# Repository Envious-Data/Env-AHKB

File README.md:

# Env-AHKB
 A keyboard that uses a HappyHackingKeyBoard inspired layout

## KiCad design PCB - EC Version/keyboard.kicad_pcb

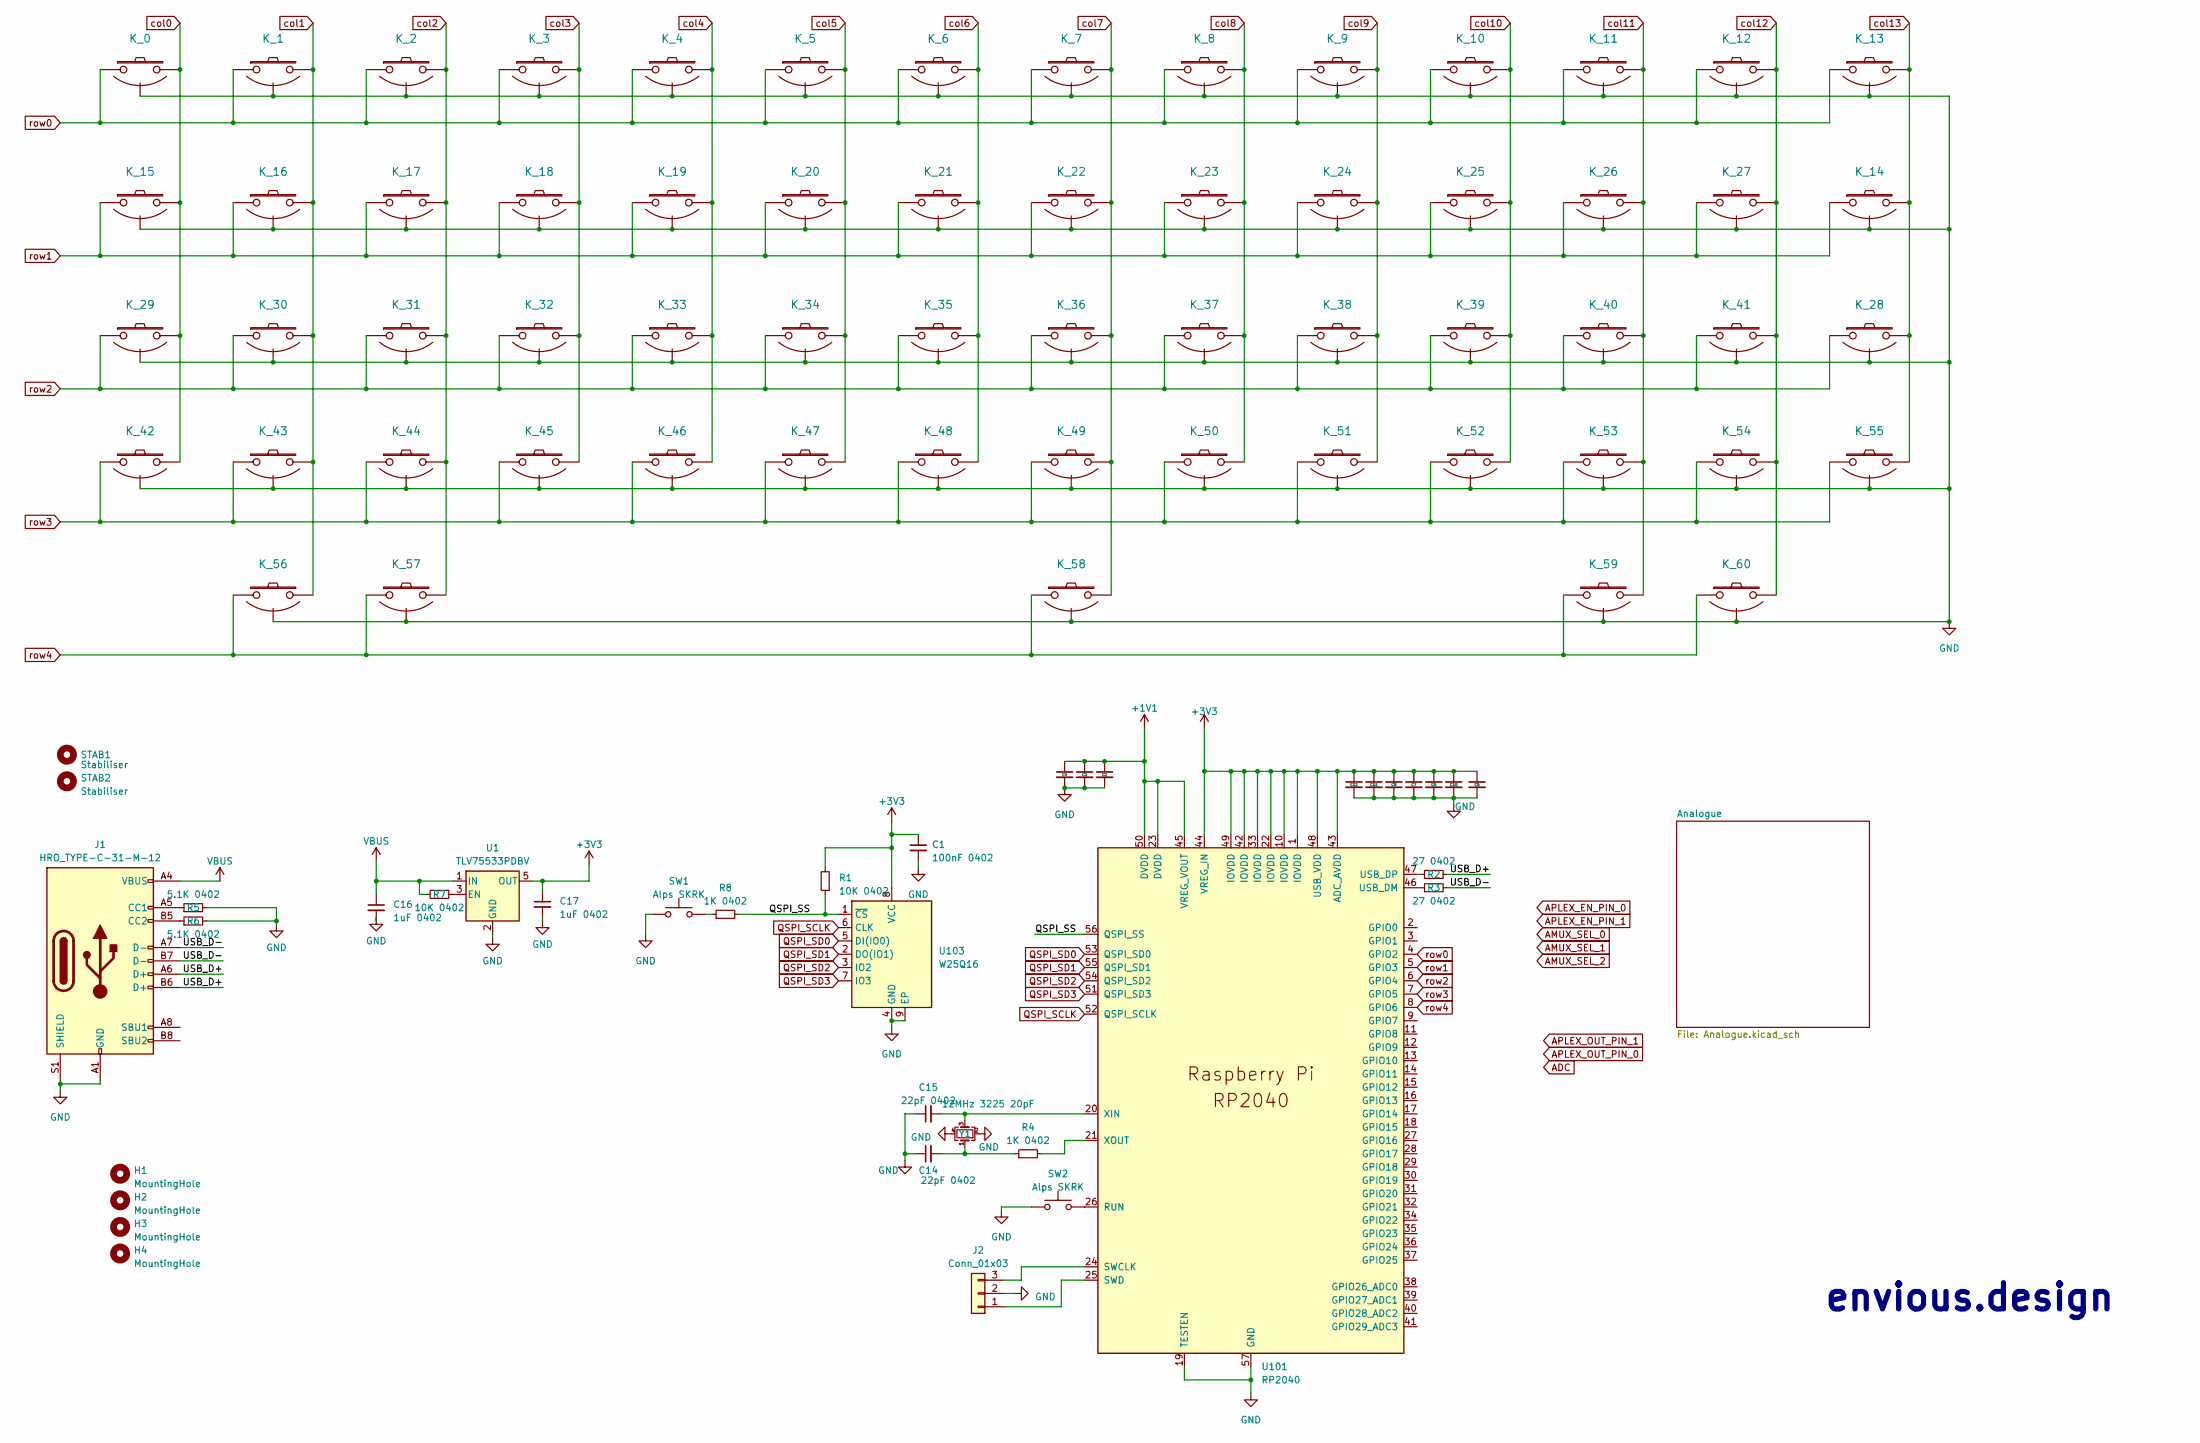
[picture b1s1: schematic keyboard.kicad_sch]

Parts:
C1, C3, C4, C6, C7, C8, C10, C11, C12: 100nF 0402; C_0402_1005Metric
C2, C5, C16, C17: 1uF 0402; C_0402_1005Metric
C14, C15: 22pF 0402; C_0402_1005Metric
H1, H2, H3, H4: MountingHole; MountingHole_3.5mm_Pad
J1: HRO_TYPE-C-31-M-12; USB_C_Receptacle_HRO_TYPE-C-31-M-12
J2: Conn_01x03; PinHeader_1x03_P2.54mm_Vertical
K_0, K_1, K_2, K_3, K_4, K_5, K_6, K_7, K_8, K_9, K_10, K_11, K_12, K_13, K_14, K_15, K_16, K_17, K_18, K_19, K_20, K_21, K_22, K_23, K_24, K_25, K_26, K_27, K_28, K_29, K_30, K_31, K_32, K_33, K_34, K_35, K_36, K_37, K_38, K_39, K_40, K_41, K_42, K_43, K_44, K_45, K_46, K_47, K_48, K_49, K_50, K_51, K_52, K_53, K_54, K_55, K_56, K_57, K_58, K_59, K_60: KEYSW; ecs_pad_1U_no_ring
R1, R7: 10K 0402; R_0402_1005Metric
R2, R3: 27 0402; R_0402_1005Metric
R4, R8: 1K 0402; R_0402_1005Metric
R5, R6: 5.1K 0402; R_0402_1005Metric
STAB1: Stabiliser; Stabilizer_Cherry_MX_7u
STAB2: Stabiliser; Stabilizer_Cherry_MX_2u
SW1, SW2: Alps SKRK; SW_Push_SPST_NO_Alps_SKRK
U1: TLV75533PDBV; SOT-23-5
U101: RP2040; RP2040-QFN-56
U103: W25Q16; SON-8-1EP_3x2mm_P0.5mm_EP1.4x1.6mm
Y1: 12MHz 3225 20pF; Crystal_SMD_3225-4Pin_3.2x2.5mm

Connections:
+1V1: C2.1, C3.1, C4.1, U101.23 (DVDD), U101.45 (VREG_VOUT), U101.50 (DVDD)
/QSPI_SS: R1.1, R8.2, U101.56 (QSPI_SS), U103.1 (~CS)
/USB_D+: J1.A6 (D+), J1.B6 (D+), R2.2
/USB_D-: J1.A7 (D-), J1.B7 (D-), R3.2
GND: C1.2, C2.2, C3.2, C4.2, C5.2, C6.2, C7.2, C8.2, C10.2, C11.2, C12.2, C14.1, C15.1, C16.2, C17.2, J1.A1 (GND), J1.A12 (GND), J1.B1 (GND), J1.B12 (GND), J1.S1 (SHIELD), J2.2, K_0.3 (SG), K_1.3 (SG), K_2.3 (SG), K_3.3 (SG), K_4.3 (SG), K_5.3 (SG), K_6.3 (SG), K_7.3 (SG), K_8.3 (SG), K_9.3 (SG), K_10.3 (SG), K_11.3 (SG), K_12.3 (SG), K_13.3 (SG), K_14.3 (SG), K_15.3 (SG), K_16.3 (SG), K_17.3 (SG), K_18.3 (SG), K_19.3 (SG), K_20.3 (SG), K_21.3 (SG), K_22.3 (SG), K_23.3 (SG), K_24.3 (SG), K_25.3 (SG), K_26.3 (SG), K_27.3 (SG), K_28.3 (SG), K_29.3 (SG), K_30.3 (SG), K_31.3 (SG), K_32.3 (SG), K_33.3 (SG), K_34.3 (SG), K_35.3 (SG), K_36.3 (SG), K_37.3 (SG), K_38.3 (SG), K_39.3 (SG), K_40.3 (SG), K_41.3 (SG), K_42.3 (SG), K_43.3 (SG), K_44.3 (SG), K_45.3 (SG), K_46.3 (SG), K_47.3 (SG), K_48.3 (SG), K_49.3 (SG), K_50.3 (SG), K_51.3 (SG), K_52.3 (SG), K_53.3 (SG), K_54.3 (SG), K_55.3 (SG), K_56.3 (SG), K_57.3 (SG), K_58.3 (SG), K_59.3 (SG), K_60.3 (SG), R5.2, R6.2, SW1.1, SW2.1, U1.2 (GND), U101.19 (TESTEN), U101.57 (GND), U103.4 (GND), U103.9 (EP), Y1.2, Y1.4; also elsewhere on the board
unnamed: C14.2, R4.1, Y1.1
unnamed: J1.A5 (CC1), R5.1
unnamed: J1.B5 (CC2), R6.1
unnamed: J2.1, U101.25 (SWD)
unnamed: J2.3, U101.24 (SWCLK)
unnamed: R8.1, SW1.2
unnamed: R7.1, U1.3 (EN)
unnamed: SW2.2, U101.26 (RUN)
unnamed: R3.1, U101.46 (USB_DM)
unnamed: R2.1, U101.47 (USB_DP)
unnamed: C15.2, U101.20 (XIN), Y1.3
unnamed: R4.2, U101.21 (XOUT)
QSPI_SCLK: U101.52 (QSPI_SCLK), U103.6 (CLK)
QSPI_SD0: U101.53 (QSPI_SD0), U103.5 (DI(IO0))
QSPI_SD1: U101.55 (QSPI_SD1), U103.2 (DO(IO1))
QSPI_SD2: U101.54 (QSPI_SD2), U103.3 (IO2)
QSPI_SD3: U101.51 (QSPI_SD3), U103.7 (IO3)
VBUS: C16.1, J1.A4 (VBUS), J1.A9 (VBUS), J1.B4 (VBUS), J1.B9 (VBUS), R7.2, U1.1 (IN)
col0: K_0.2, K_15.2, K_29.2, K_42.2; also elsewhere on the board
col1: K_1.2, K_16.2, K_30.2, K_43.2, K_56.2; also elsewhere on the board
col2: K_2.2, K_17.2, K_31.2, K_44.2, K_57.2; also elsewhere on the board
col3: K_3.2, K_18.2, K_32.2, K_45.2; also elsewhere on the board
col4: K_4.2, K_19.2, K_33.2, K_46.2; also elsewhere on the board
col5: K_5.2, K_20.2, K_34.2, K_47.2; also elsewhere on the board
col6: K_6.2, K_21.2, K_35.2, K_48.2; also elsewhere on the board
col7: K_7.2, K_22.2, K_36.2, K_49.2, K_58.2; also elsewhere on the board
col8: K_8.2, K_23.2, K_37.2, K_50.2; also elsewhere on the board
col9: K_9.2, K_24.2, K_38.2, K_51.2; also elsewhere on the board
col10: K_10.2, K_25.2, K_39.2, K_52.2; also elsewhere on the board
col11: K_11.2, K_26.2, K_40.2, K_53.2, K_59.2; also elsewhere on the board
col12: K_12.2, K_27.2, K_41.2, K_54.2, K_60.2; also elsewhere on the board
col13: K_13.2, K_14.2, K_28.2, K_55.2; also elsewhere on the board
row0: K_0.1, K_1.1, K_2.1, K_3.1, K_4.1, K_5.1, K_6.1, K_7.1, K_8.1, K_9.1, K_10.1, K_11.1, K_12.1, K_13.1, U101.4 (GPIO2)
row1: K_14.1, K_15.1, K_16.1, K_17.1, K_18.1, K_19.1, K_20.1, K_21.1, K_22.1, K_23.1, K_24.1, K_25.1, K_26.1, K_27.1, U101.5 (GPIO3)
row2: K_28.1, K_29.1, K_30.1, K_31.1, K_32.1, K_33.1, K_34.1, K_35.1, K_36.1, K_37.1, K_38.1, K_39.1, K_40.1, K_41.1, U101.6 (GPIO4)
row3: K_42.1, K_43.1, K_44.1, K_45.1, K_46.1, K_47.1, K_48.1, K_49.1, K_50.1, K_51.1, K_52.1, K_53.1, K_54.1, K_55.1, U101.7 (GPIO5)
row4: K_56.1, K_57.1, K_58.1, K_59.1, K_60.1, U101.8 (GPIO6)

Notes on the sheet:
envious.design

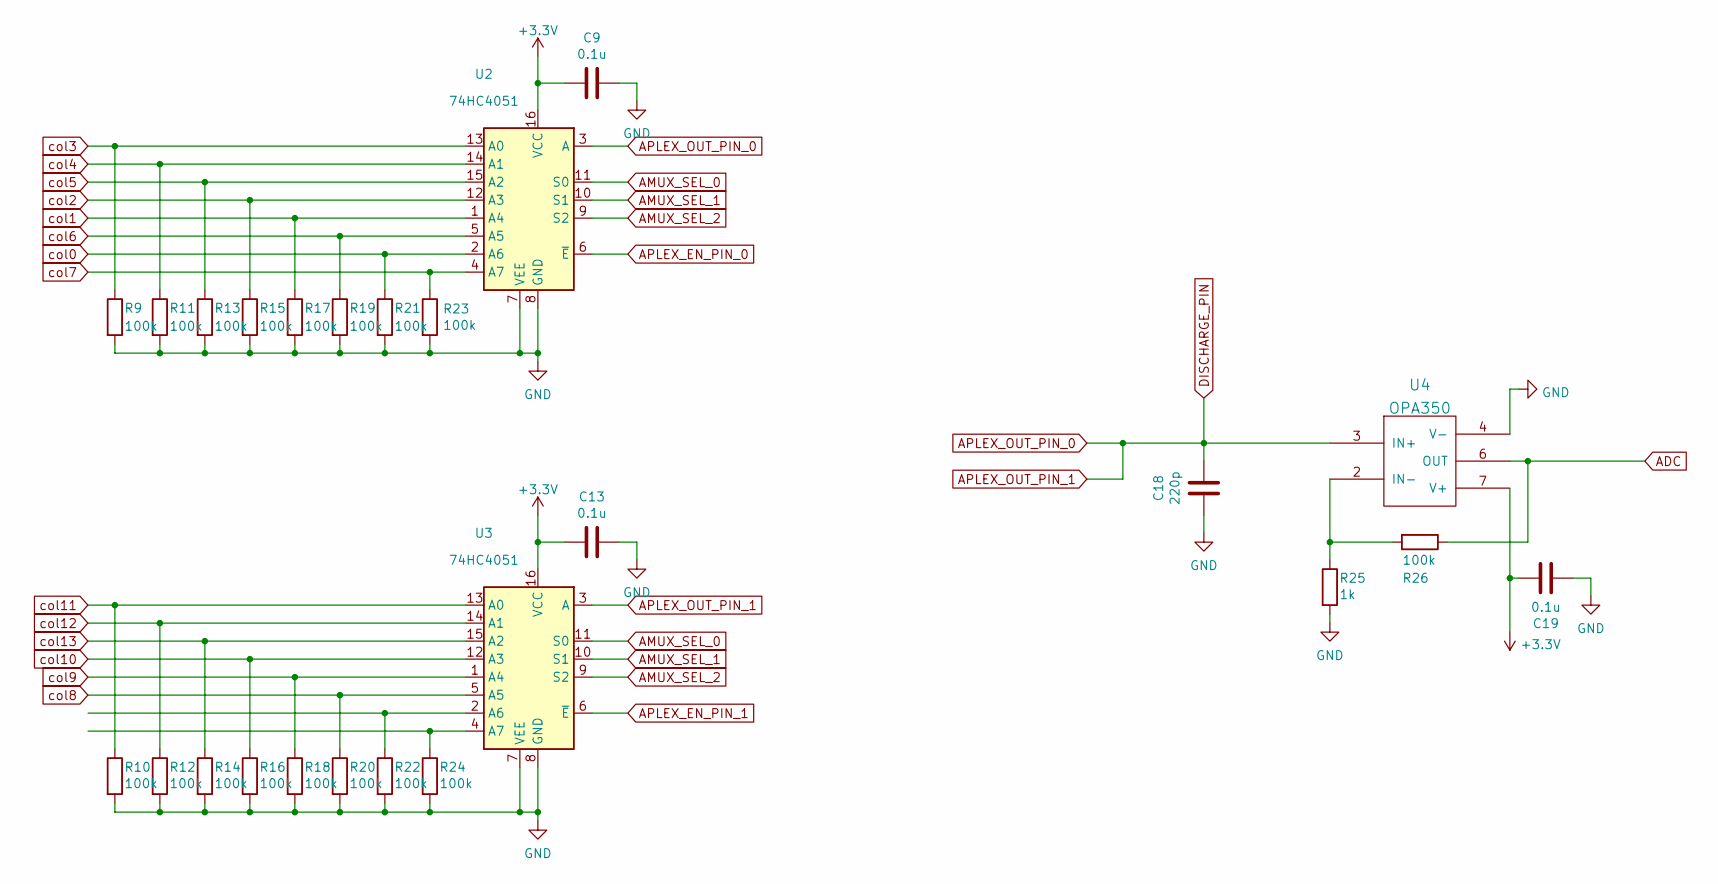
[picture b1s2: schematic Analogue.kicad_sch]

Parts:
C9, C13, C19: 0.1u; C_0603_1608Metric
C18: 220p; C_0603_1608Metric
R9, R10, R11, R12, R13, R14, R15, R16, R17, R18, R19, R20, R21, R22, R23, R24, R26: 100k; R_0603_1608Metric
R25: 1k; R_0603_1608Metric
U2, U3: 74HC4051; TSSOP16
U4: OPA350; SOIC-8_3.9x4.9mm_P1.27mm

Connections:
ADC: R26.1, U4.6 (OUT)
AMUX_SEL_0: U2.11 (S0), U3.11 (S0)
AMUX_SEL_1: U2.10 (S1), U3.10 (S1)
AMUX_SEL_2: U2.9 (S2), U3.9 (S2)
APLEX_EN_PIN_0: U2.6 (~E)
APLEX_EN_PIN_1: U3.6 (~E)
APLEX_OUT_PIN_0: C18.1, U2.3 (A), U3.3 (A), U4.3 (IN+)
GND: C9.1, C13.1, C18.2, C19.1, R9.2, R10.2, R11.2, R12.2, R13.2, R14.2, R15.2, R16.2, R17.2, R18.2, R19.2, R20.2, R21.2, R22.2, R23.2, R24.2, R25.2, U2.7 (VEE), U2.8 (GND), U3.7 (VEE), U3.8 (GND), U4.4 (V-); also elsewhere on the board
unnamed: R22.1, U3.2 (A6)
unnamed: R24.1, U3.4 (A7)
unnamed: R25.1, R26.2, U4.2 (IN-)
col0: R21.1, U2.2 (A6); also elsewhere on the board
col1: R17.1, U2.1 (A4); also elsewhere on the board
col2: R15.1, U2.12 (A3); also elsewhere on the board
col3: R9.1, U2.13 (A0); also elsewhere on the board
col4: R11.1, U2.14 (A1); also elsewhere on the board
col5: R13.1, U2.15 (A2); also elsewhere on the board
col6: R19.1, U2.5 (A5); also elsewhere on the board
col7: R23.1, U2.4 (A7); also elsewhere on the board
col8: R20.1, U3.5 (A5); also elsewhere on the board
col9: R18.1, U3.1 (A4); also elsewhere on the board
col10: R16.1, U3.12 (A3); also elsewhere on the board
col11: R10.1, U3.13 (A0); also elsewhere on the board
col12: R12.1, U3.14 (A1); also elsewhere on the board
col13: R14.1, U3.15 (A2); also elsewhere on the board

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
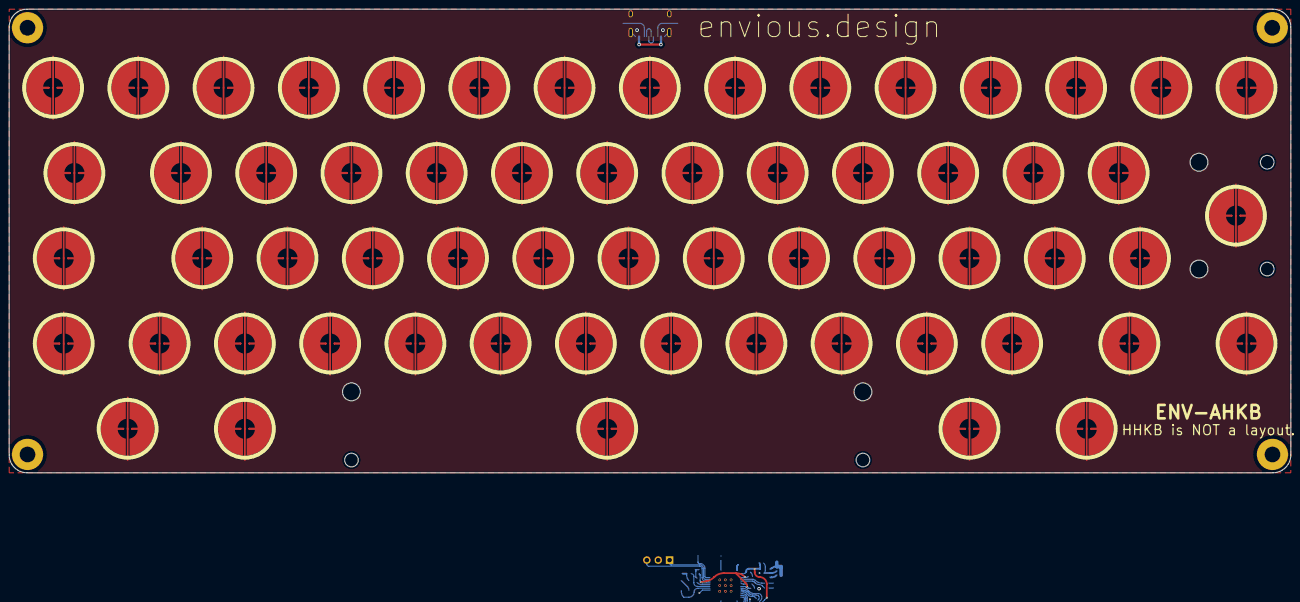
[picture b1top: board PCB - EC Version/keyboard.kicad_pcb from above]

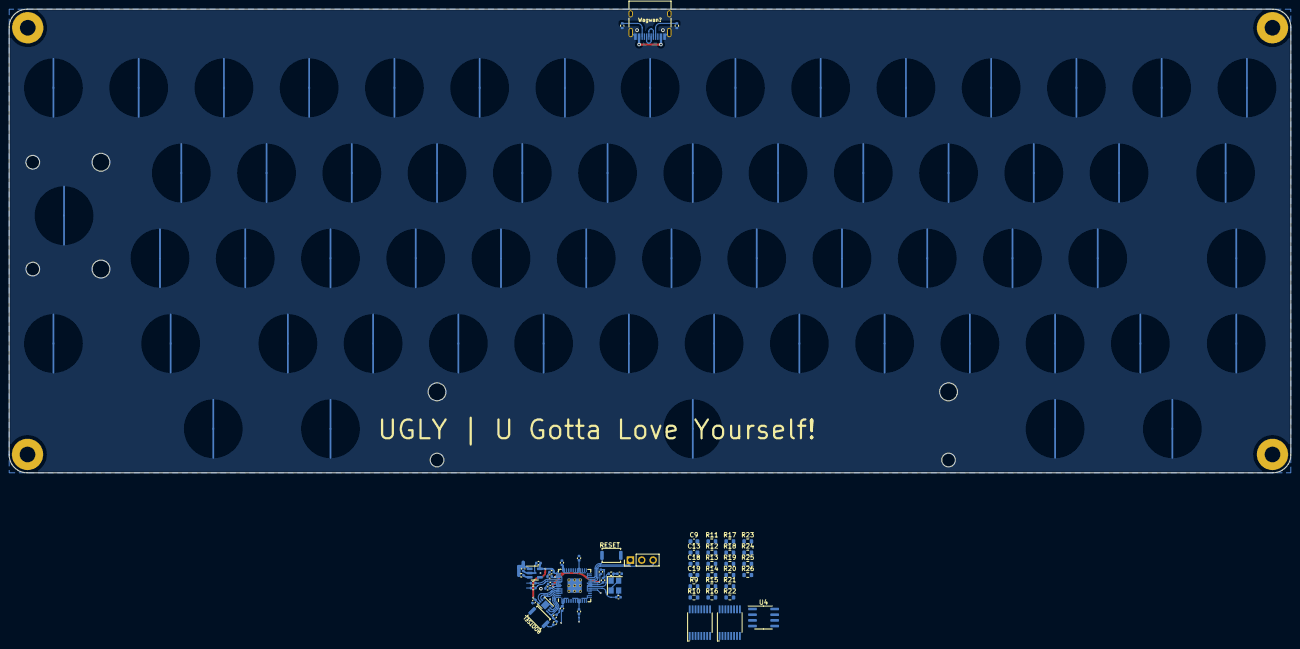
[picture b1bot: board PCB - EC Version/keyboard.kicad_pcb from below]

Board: 2 copper layers, 286.4 x 103.6 mm, 123 parts (56 on the bottom side), 51 nets.

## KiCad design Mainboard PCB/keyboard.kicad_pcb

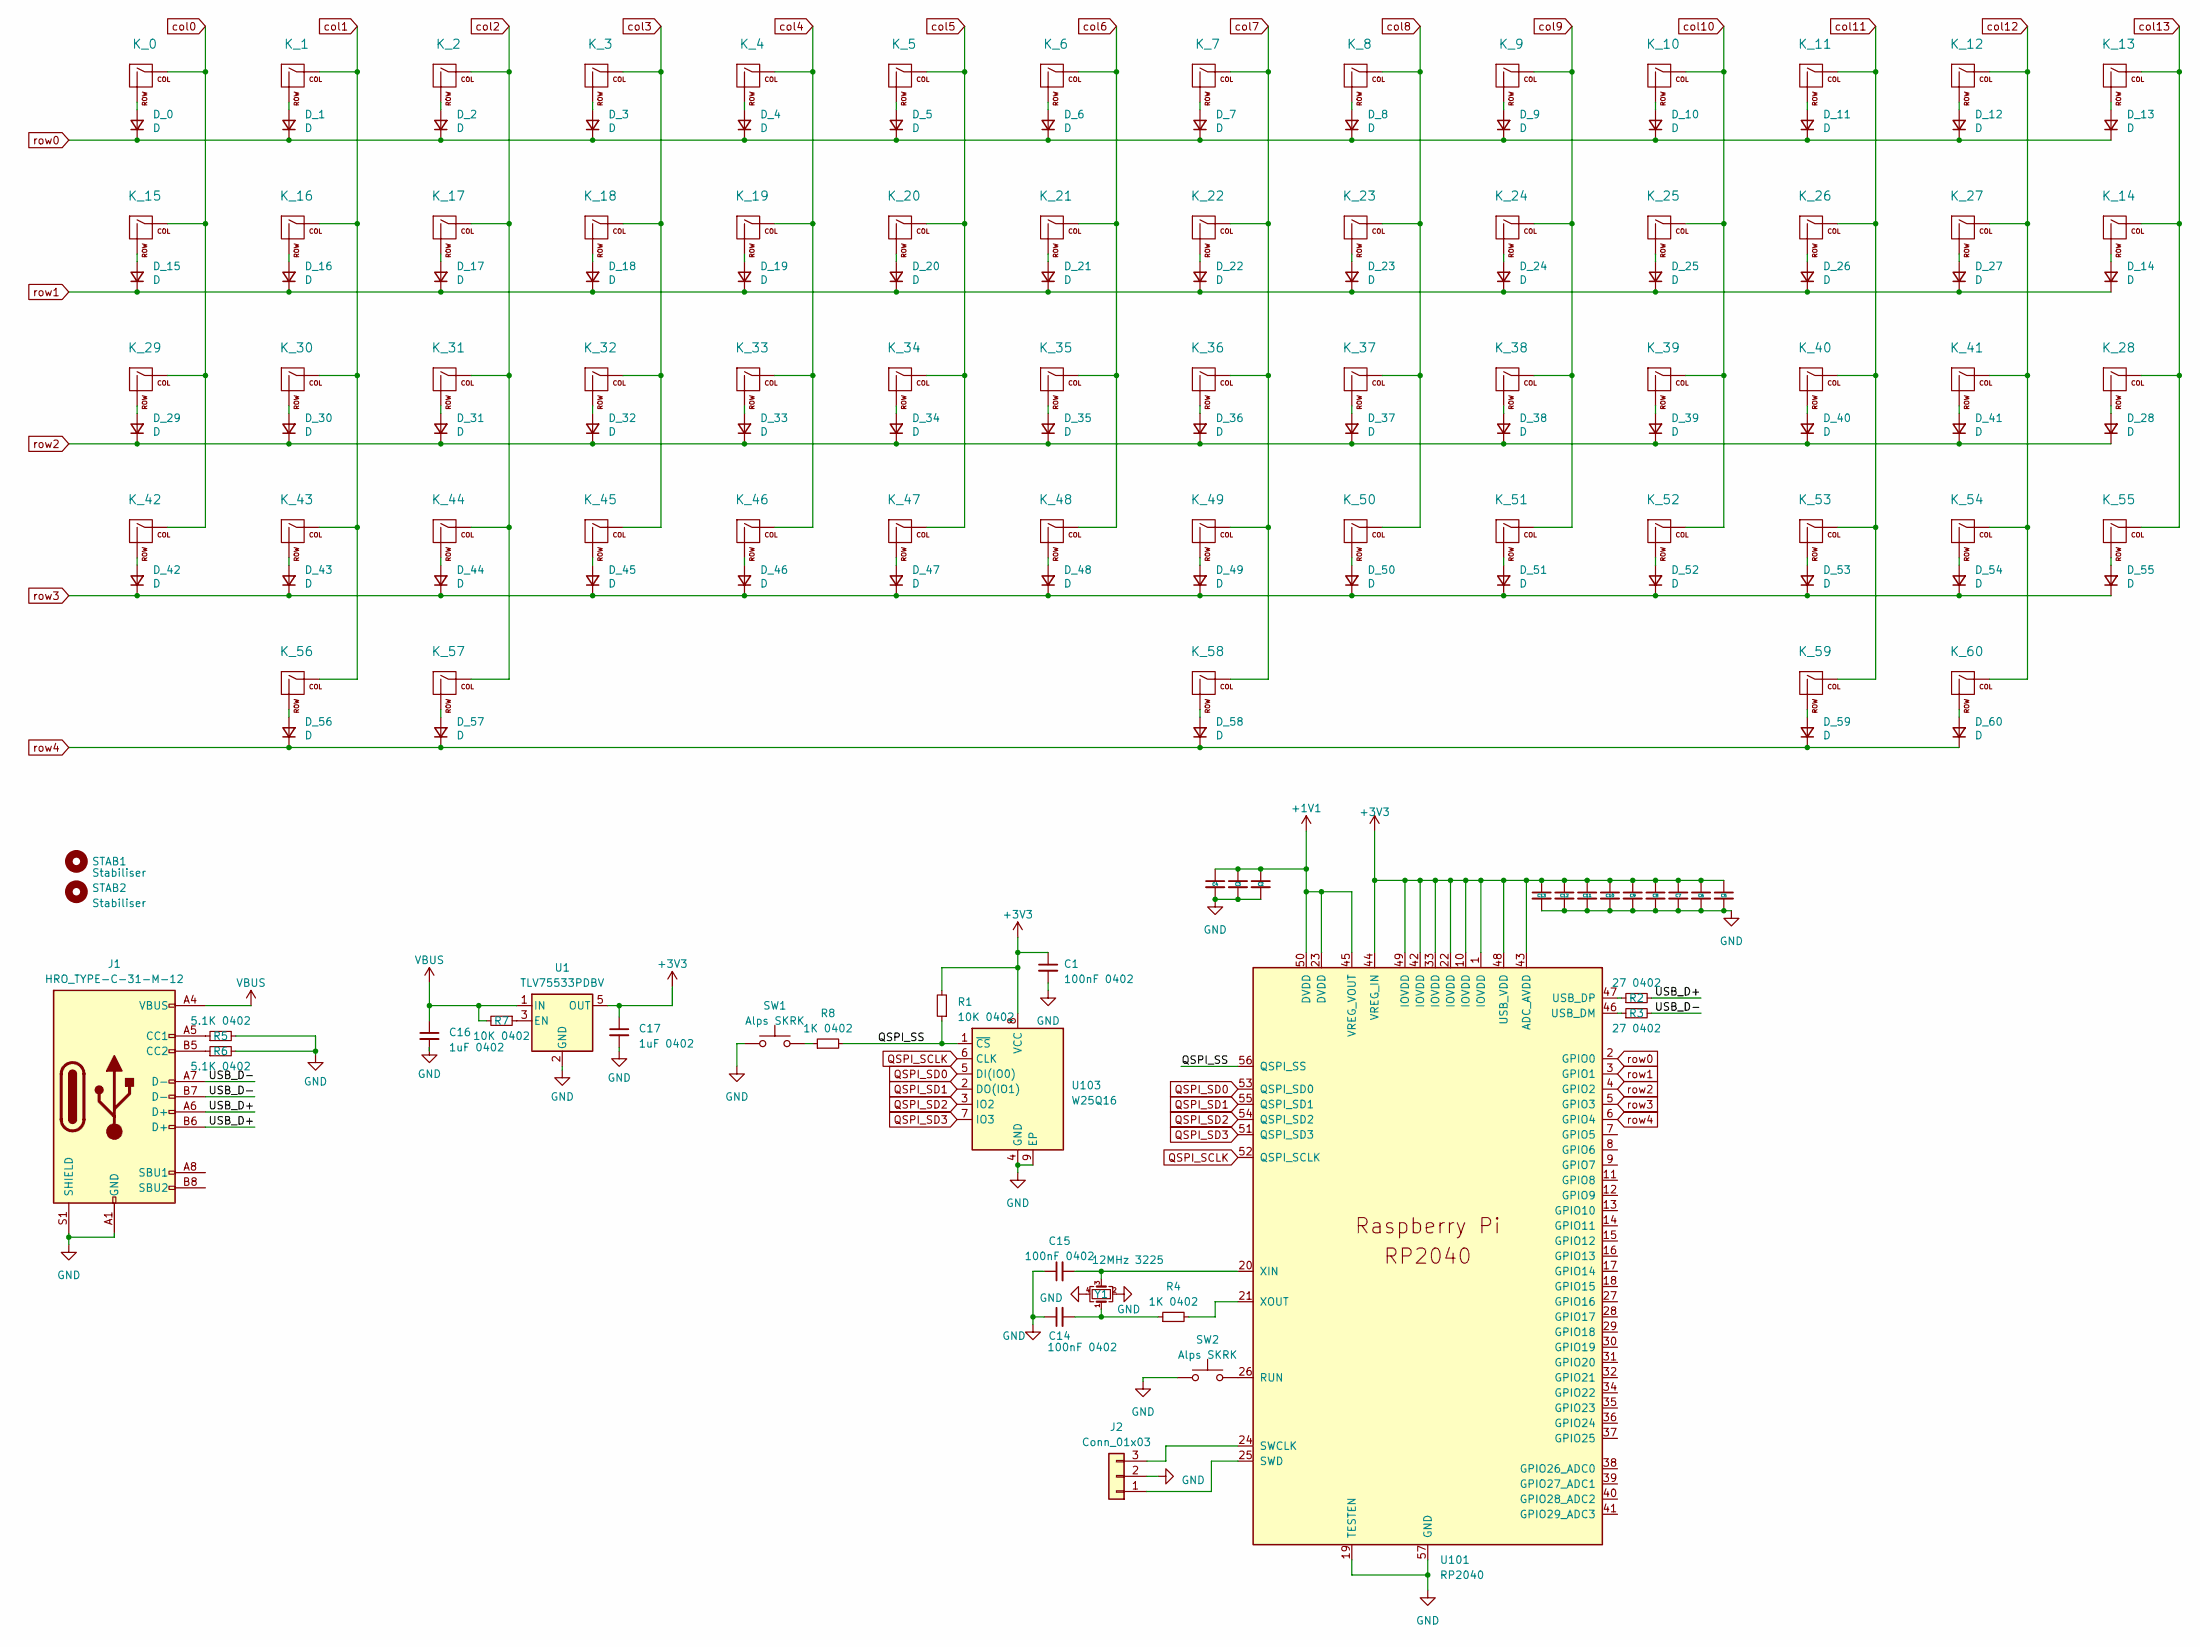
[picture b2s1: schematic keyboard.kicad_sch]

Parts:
C1, C3, C4, C6, C7, C8, C9, C10, C11, C12, C13, C14, C15: 100nF 0402; C_0402_1005Metric
C2, C5, C16, C17: 1uF 0402; C_0402_1005Metric
D_0, D_1, D_2, D_3, D_4, D_5, D_6, D_7, D_8, D_9, D_10, D_11, D_12, D_13, D_14, D_15, D_16, D_17, D_18, D_19, D_20, D_21, D_22, D_23, D_24, D_25, D_26, D_27, D_28, D_29, D_30, D_31, D_32, D_33, D_34, D_35, D_36, D_37, D_38, D_39, D_40, D_41, D_42, D_43, D_44, D_45, D_46, D_47, D_48, D_49, D_50, D_51, D_52, D_53, D_54, D_55, D_56, D_57, D_58, D_59, D_60: D; D_SOD-123
J1: HRO_TYPE-C-31-M-12; USB_C_Receptacle_HRO_TYPE-C-31-M-12
J2: Conn_01x03; PinHeader_1x03_P2.54mm_Vertical
K_0, K_1, K_2, K_3, K_4, K_5, K_6, K_7, K_8, K_9, K_10, K_11, K_12, K_13, K_14, K_15, K_16, K_17, K_18, K_19, K_20, K_21, K_22, K_23, K_24, K_25, K_26, K_27, K_28, K_29, K_30, K_31, K_32, K_33, K_34, K_35, K_36, K_37, K_38, K_39, K_40, K_41, K_42, K_43, K_44, K_45, K_46, K_47, K_48, K_49, K_50, K_51, K_52, K_53, K_54, K_55, K_56, K_57, K_58, K_59, K_60: KEYSW; MXOnly-1U-NoLED
R1, R7: 10K 0402; R_0402_1005Metric
R2, R3: 27 0402; R_0402_1005Metric
R4, R8: 1K 0402; R_0402_1005Metric
R5, R6: 5.1K 0402; R_0402_1005Metric
STAB1: Stabiliser; Stabilizer_Cherry_MX_7u
STAB2: Stabiliser; Stabilizer_Cherry_MX_2u
SW1, SW2: Alps SKRK; SW_Push_SPST_NO_Alps_SKRK
U1: TLV75533PDBV; SOT-23-5
U101: RP2040; RP2040-QFN-56
U103: W25Q16; SON-8-1EP_3x2mm_P0.5mm_EP1.4x1.6mm
Y1: 12MHz 3225; Crystal_SMD_3225-4Pin_3.2x2.5mm

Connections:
+1V1: C2.1, C3.1, C4.1, U101.23 (DVDD), U101.45 (VREG_VOUT), U101.50 (DVDD)
+3V3: C1.1, C5.1, C6.1, C7.1, C8.1, C9.1, C10.1, C11.1, C12.1, C13.1, C17.1, R1.2, U1.5 (OUT), U101.1 (IOVDD), U101.10 (IOVDD), U101.22 (IOVDD), U101.33 (IOVDD), U101.42 (IOVDD), U101.43 (ADC_AVDD), U101.44 (VREG_IN), U101.48 (USB_VDD), U101.49 (IOVDD), U103.8 (VCC); also elsewhere on the board
/QSPI_SS: R1.1, R8.2, U101.56 (QSPI_SS), U103.1 (~CS)
/USB_D+: J1.A6 (D+), J1.B6 (D+), R2.2
/USB_D-: J1.A7 (D-), J1.B7 (D-), R3.2
GND: C1.2, C2.2, C3.2, C4.2, C5.2, C6.2, C7.2, C8.2, C9.2, C10.2, C11.2, C12.2, C13.2, C14.1, C15.1, C16.2, C17.2, J1.A1 (GND), J1.A12 (GND), J1.B1 (GND), J1.B12 (GND), J1.S1 (SHIELD), J2.2, R5.2, R6.2, SW1.1, SW2.1, U1.2 (GND), U101.19 (TESTEN), U101.57 (GND), U103.4 (GND), U103.9 (EP), Y1.2, Y1.4; also elsewhere on the board
unnamed: C14.2, R4.1, Y1.1
unnamed: D_0.2 (A), K_0.2 (ROW)
unnamed: D_1.2 (A), K_1.2 (ROW)
unnamed: D_2.2 (A), K_2.2 (ROW)
unnamed: D_3.2 (A), K_3.2 (ROW)
unnamed: D_4.2 (A), K_4.2 (ROW)
unnamed: D_5.2 (A), K_5.2 (ROW)
unnamed: D_6.2 (A), K_6.2 (ROW)
unnamed: D_7.2 (A), K_7.2 (ROW)
unnamed: D_8.2 (A), K_8.2 (ROW)
unnamed: D_9.2 (A), K_9.2 (ROW)
unnamed: D_10.2 (A), K_10.2 (ROW)
unnamed: D_11.2 (A), K_11.2 (ROW)
unnamed: D_12.2 (A), K_12.2 (ROW)
unnamed: D_13.2 (A), K_13.2 (ROW)
unnamed: D_14.2 (A), K_14.2 (ROW)
unnamed: D_15.2 (A), K_15.2 (ROW)
unnamed: D_16.2 (A), K_16.2 (ROW)
unnamed: D_17.2 (A), K_17.2 (ROW)
unnamed: D_18.2 (A), K_18.2 (ROW)
unnamed: D_19.2 (A), K_19.2 (ROW)
unnamed: D_20.2 (A), K_20.2 (ROW)
unnamed: D_21.2 (A), K_21.2 (ROW)
unnamed: D_22.2 (A), K_22.2 (ROW)
unnamed: D_23.2 (A), K_23.2 (ROW)
unnamed: D_24.2 (A), K_24.2 (ROW)
unnamed: D_25.2 (A), K_25.2 (ROW)
unnamed: D_26.2 (A), K_26.2 (ROW)
unnamed: D_27.2 (A), K_27.2 (ROW)
unnamed: D_28.2 (A), K_28.2 (ROW)
unnamed: D_29.2 (A), K_29.2 (ROW)
unnamed: D_30.2 (A), K_30.2 (ROW)
unnamed: D_31.2 (A), K_31.2 (ROW)
unnamed: D_32.2 (A), K_32.2 (ROW)
unnamed: D_33.2 (A), K_33.2 (ROW)
unnamed: D_34.2 (A), K_34.2 (ROW)
unnamed: D_35.2 (A), K_35.2 (ROW)
unnamed: D_36.2 (A), K_36.2 (ROW)
unnamed: D_37.2 (A), K_37.2 (ROW)
unnamed: D_38.2 (A), K_38.2 (ROW)
unnamed: D_39.2 (A), K_39.2 (ROW)
unnamed: D_40.2 (A), K_40.2 (ROW)
unnamed: D_41.2 (A), K_41.2 (ROW)
unnamed: D_42.2 (A), K_42.2 (ROW)
unnamed: D_43.2 (A), K_43.2 (ROW)
unnamed: D_44.2 (A), K_44.2 (ROW)
unnamed: D_45.2 (A), K_45.2 (ROW)
unnamed: D_46.2 (A), K_46.2 (ROW)
unnamed: D_47.2 (A), K_47.2 (ROW)
unnamed: D_48.2 (A), K_48.2 (ROW)
unnamed: D_49.2 (A), K_49.2 (ROW)
unnamed: D_50.2 (A), K_50.2 (ROW)
unnamed: D_51.2 (A), K_51.2 (ROW)
unnamed: D_52.2 (A), K_52.2 (ROW)
unnamed: D_53.2 (A), K_53.2 (ROW)
unnamed: D_54.2 (A), K_54.2 (ROW)
unnamed: D_55.2 (A), K_55.2 (ROW)
unnamed: D_56.2 (A), K_56.2 (ROW)
unnamed: D_57.2 (A), K_57.2 (ROW)
unnamed: D_58.2 (A), K_58.2 (ROW)
unnamed: D_59.2 (A), K_59.2 (ROW)
unnamed: D_60.2 (A), K_60.2 (ROW)
unnamed: J1.A5 (CC1), R5.1
unnamed: J1.B5 (CC2), R6.1
unnamed: J2.1, U101.25 (SWD)
unnamed: J2.3, U101.24 (SWCLK)
unnamed: R8.1, SW1.2
unnamed: R7.1, U1.3 (EN)
unnamed: SW2.2, U101.26 (RUN)
unnamed: R3.1, U101.46 (USB_DM)
unnamed: R2.1, U101.47 (USB_DP)
unnamed: C15.2, U101.20 (XIN), Y1.3
unnamed: R4.2, U101.21 (XOUT)
QSPI_SCLK: U101.52 (QSPI_SCLK), U103.6 (CLK)
QSPI_SD0: U101.53 (QSPI_SD0), U103.5 (DI(IO0))
QSPI_SD1: U101.55 (QSPI_SD1), U103.2 (DO(IO1))
QSPI_SD2: U101.54 (QSPI_SD2), U103.3 (IO2)
QSPI_SD3: U101.51 (QSPI_SD3), U103.7 (IO3)
VBUS: C16.1, J1.A4 (VBUS), J1.A9 (VBUS), J1.B4 (VBUS), J1.B9 (VBUS), R7.2, U1.1 (IN)
col0: K_0.1 (COL), K_15.1 (COL), K_29.1 (COL), K_42.1 (COL)
col1: K_1.1 (COL), K_16.1 (COL), K_30.1 (COL), K_43.1 (COL), K_56.1 (COL)
col2: K_2.1 (COL), K_17.1 (COL), K_31.1 (COL), K_44.1 (COL), K_57.1 (COL)
col3: K_3.1 (COL), K_18.1 (COL), K_32.1 (COL), K_45.1 (COL)
col4: K_4.1 (COL), K_19.1 (COL), K_33.1 (COL), K_46.1 (COL)
col5: K_5.1 (COL), K_20.1 (COL), K_34.1 (COL), K_47.1 (COL)
col6: K_6.1 (COL), K_21.1 (COL), K_35.1 (COL), K_48.1 (COL)
col7: K_7.1 (COL), K_22.1 (COL), K_36.1 (COL), K_49.1 (COL), K_58.1 (COL)
col8: K_8.1 (COL), K_23.1 (COL), K_37.1 (COL), K_50.1 (COL)
col9: K_9.1 (COL), K_24.1 (COL), K_38.1 (COL), K_51.1 (COL)
col10: K_10.1 (COL), K_25.1 (COL), K_39.1 (COL), K_52.1 (COL)
col11: K_11.1 (COL), K_26.1 (COL), K_40.1 (COL), K_53.1 (COL), K_59.1 (COL)
col12: K_12.1 (COL), K_27.1 (COL), K_41.1 (COL), K_54.1 (COL), K_60.1 (COL)
col13: K_13.1 (COL), K_14.1 (COL), K_28.1 (COL), K_55.1 (COL)
row0: D_0.1 (K), D_1.1 (K), D_2.1 (K), D_3.1 (K), D_4.1 (K), D_5.1 (K), D_6.1 (K), D_7.1 (K), D_8.1 (K), D_9.1 (K), D_10.1 (K), D_11.1 (K), D_12.1 (K), D_13.1 (K), U101.2 (GPIO0)
row1: D_14.1 (K), D_15.1 (K), D_16.1 (K), D_17.1 (K), D_18.1 (K), D_19.1 (K), D_20.1 (K), D_21.1 (K), D_22.1 (K), D_23.1 (K), D_24.1 (K), D_25.1 (K), D_26.1 (K), D_27.1 (K), U101.3 (GPIO1)
row2: D_28.1 (K), D_29.1 (K), D_30.1 (K), D_31.1 (K), D_32.1 (K), D_33.1 (K), D_34.1 (K), D_35.1 (K), D_36.1 (K), D_37.1 (K), D_38.1 (K), D_39.1 (K), D_40.1 (K), D_41.1 (K), U101.4 (GPIO2)
row3: D_42.1 (K), D_43.1 (K), D_44.1 (K), D_45.1 (K), D_46.1 (K), D_47.1 (K), D_48.1 (K), D_49.1 (K), D_50.1 (K), D_51.1 (K), D_52.1 (K), D_53.1 (K), D_54.1 (K), D_55.1 (K), U101.5 (GPIO3)
row4: D_56.1 (K), D_57.1 (K), D_58.1 (K), D_59.1 (K), D_60.1 (K), U101.6 (GPIO4)

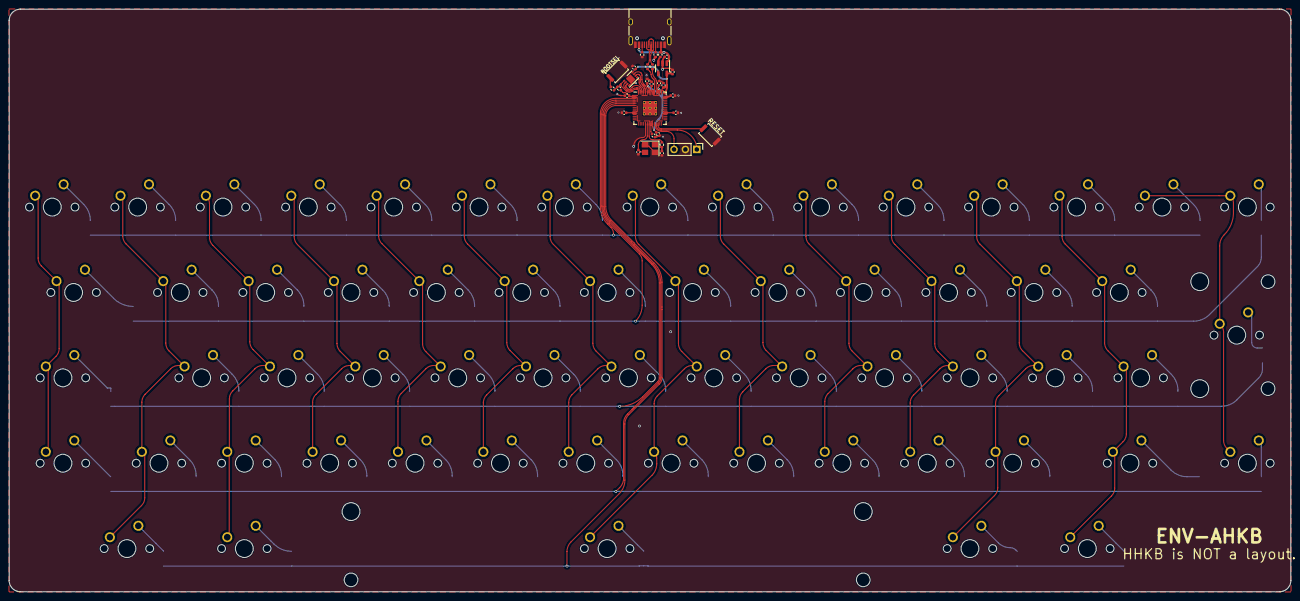
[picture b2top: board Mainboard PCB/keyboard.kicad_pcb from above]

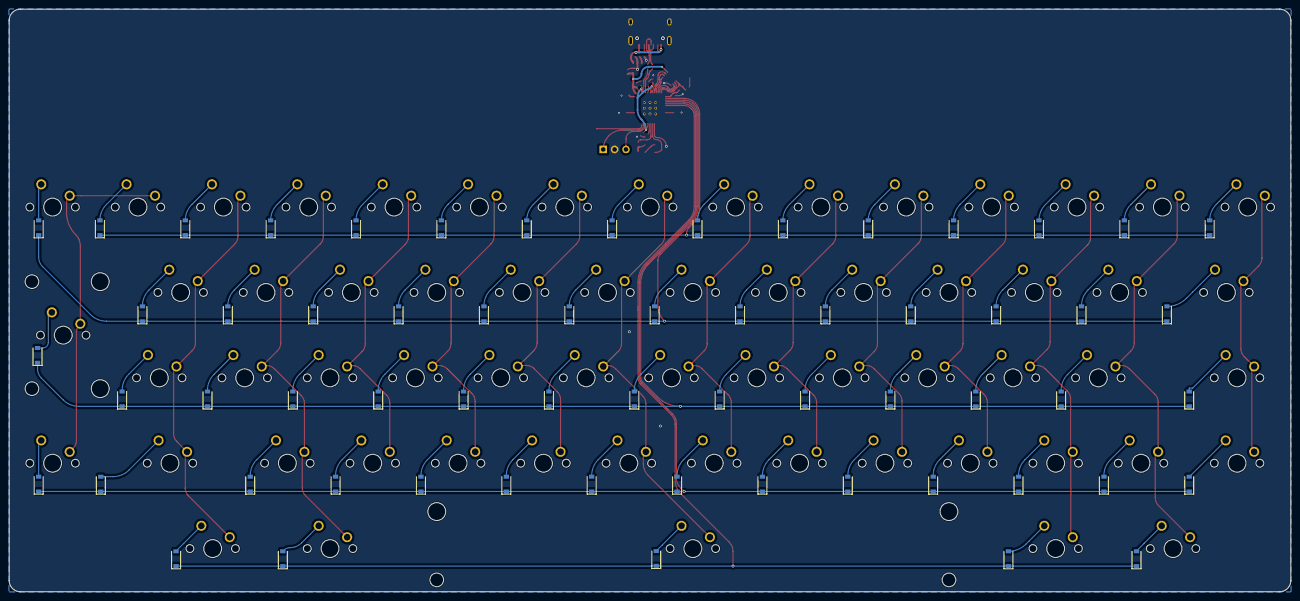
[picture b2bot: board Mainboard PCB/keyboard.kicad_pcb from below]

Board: 2 copper layers, 286.0 x 130.0 mm, 155 parts (61 on the bottom side), 104 nets.

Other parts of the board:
C6#2: 100nF 0402; C_0402_1005Metric

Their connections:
+3V3: C6#2.1; also elsewhere on the board
GND: C6#2.2; also elsewhere on the board

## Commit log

2023-03-07 +1 initial commit
2023-03-07 routed all traces needed thus far among other things required
2023-03-07 added power circuit for solenoids
2023-03-07 added power circuitry for 6 solenoids
2023-03-07 added correct sized cap and generated gerber + BOM
2023-03-07 updated gerbers
2023-03-07 added some "art"
2023-03-08 renamed main board and made cost reduced version
2023-03-08 general improvements in reliability + added 5 spare gpio headder
2023-03-08 redrew some more traces
2023-03-12 various updates and adjustments, created case for board will upload later
2023-06-13 got started on EC version.
2023-06-13 couple extra bits
2023-10-06 adjusted a bunch of references
2024-04-24 fixed a little font issue
